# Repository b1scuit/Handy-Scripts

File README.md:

# B1scuit-Handy-Scripts
Just random things for random reasons

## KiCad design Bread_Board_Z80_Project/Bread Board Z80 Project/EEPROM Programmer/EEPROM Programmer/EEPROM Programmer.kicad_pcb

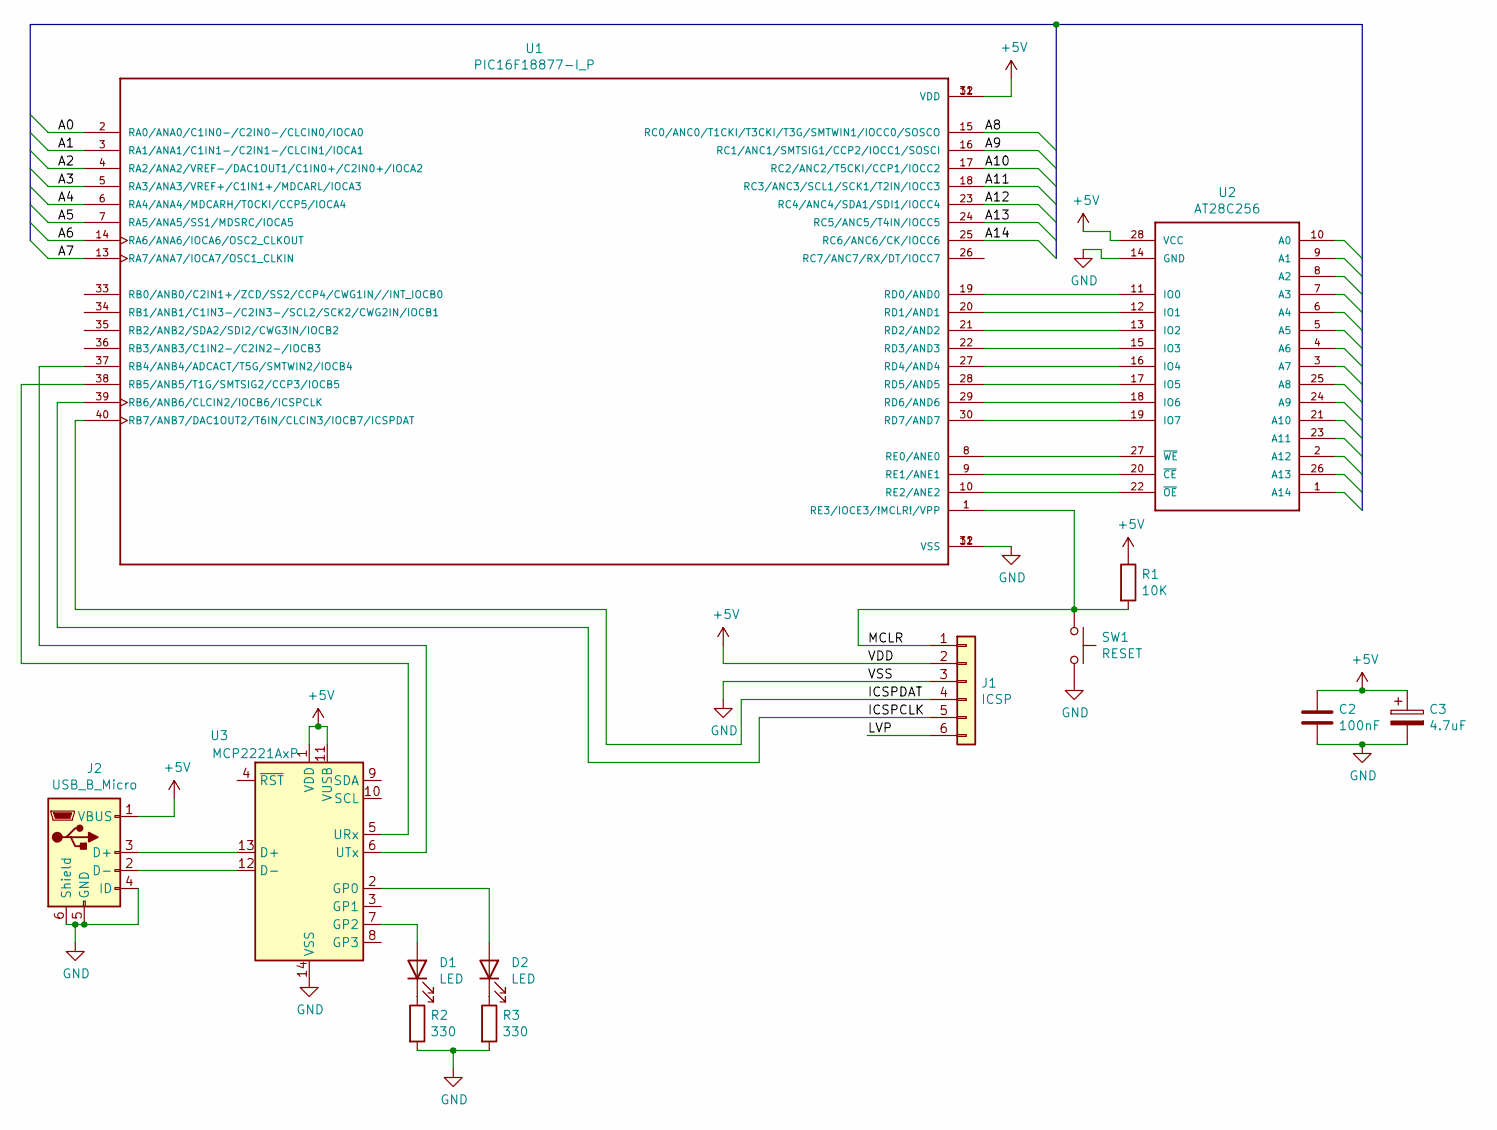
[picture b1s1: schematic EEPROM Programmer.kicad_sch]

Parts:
C2: 100nF; C_Rect_L7.0mm_W6.0mm_P5.00mm
C3: 4.7uF; C_Rect_L7.0mm_W6.0mm_P5.00mm
D1, D2: LED; LED_D8.0mm
J1: ICSP; PinHeader_1x06_P1.00mm_Horizontal
J2: USB_B_Micro; USB_Micro-AB_Molex_47590-0001
R1: 10K; R_Box_L8.4mm_W2.5mm_P5.08mm
R2, R3: 330; R_Box_L8.4mm_W2.5mm_P5.08mm
SW1: RESET; SW_SPDT_PCM12
U1: PIC16F18877-I_P; DIP-40_W15.24mm_LongPads
U2: AT28C256; DIP_Socket-28_W11.9_W12.7_W15.24_W17.78_W18.5_3M_228-1277-0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
U3: MCP2221AxP; DIP-14_W7.62mm

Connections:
+5V: C2.1, C3.1, J1.2, J2.1 (VBUS), R1.1, U1.11 (VDD), U1.32 (VDD), U2.28 (VCC), U3.1 (VDD), U3.11 (VUSB)
/A0: U1.2 (RA0/ANA0/C1IN0-/C2IN0-/CLCIN0/IOCA0)
/A1: U1.3 (RA1/ANA1/C1IN1-/C2IN1-/CLCIN1/IOCA1)
/A2: U1.4 (RA2/ANA2/VREF-/DAC1OUT1/C1IN0+/C2IN0+/I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)
/A3: U1.5 (RA3/ANA3/VREF+/C1IN1+/MDCARL/IOCA3)
/A4: U1.6 (RA4/ANA4/MDCARH/T0CKI/CCP5/IOCA4)
/A5: U1.7 (RA5/ANA5/SS1/MDSRC/IOCA5)
/A6: U1.14 (RA6/ANA6/IOCA6/OSC2_CLKOUT)
/A7: U1.13 (RA7/ANA7/IOCA7/OSC1_CLKIN)
/A8: U1.15 (RC0/ANC0/T1CKI/T3CKI/T3G/SMTWIN1/IOCC0/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)
/A9: U1.16 (RC1/ANC1/SMTSIG1/CCP2/IOCC1/SOSCI)
/A10: U1.17 (RC2/ANC2/T5CKI/CCP1/IOCC2)
/A11: U1.18 (RC3/ANC3/SCL1/SCK1/T2IN/IOCC3)
/A12: U1.23 (RC4/ANC4/SDA1/SDI1/IOCC4)
/A13: U1.24 (RC5/ANC5/T4IN/IOCC5)
/A14: U1.25 (RC6/ANC6/CK/IOCC6)
/ICSPCLK: J1.5, U1.39 (RB6/ANB6/CLCIN2/IOCB6/ICSPCLK)
/ICSPDAT: J1.4, U1.40 (RB7/ANB7/DAC1OUT2/T6IN/CLCIN3/IOCB7/ICS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)
/LVP: J1.6
/MCLR: J1.1, R1.2, SW1.1, U1.1 (RE3/IOCE3/!MCLR!/VPP)
GND: C2.2, C3.2, J1.3, J2.4 (ID), J2.5 (GND), J2.6 (Shield), R2.2, R3.2, SW1.2, U1.12 (VSS), U1.31 (VSS), U2.14 (GND), U3.14 (VSS)
unnamed: D1.2 (A), U3.7 (GP2)
unnamed: D1.1 (K), R2.1
unnamed: D2.2 (A), U3.2 (GP0)
unnamed: D2.1 (K), R3.1
unnamed: J2.3 (D+), U3.13 (D+)
unnamed: J2.2 (D-), U3.12 (D-)
unnamed: U1.37 (RB4/ANB4/ADCACT/T5G/SMTWIN2/IOCB4), U3.6 (UTx)
unnamed: U1.38 (RB5/ANB5/T1G/SMTSIG2/CCP3/IOCB5), U3.5 (URx)
unnamed: U1.19 (RD0/AND0), U2.11 (IO0)
unnamed: U1.20 (RD1/AND1), U2.12 (IO1)
unnamed: U1.21 (RD2/AND2), U2.13 (IO2)
unnamed: U1.22 (RD3/AND3), U2.15 (IO3)
unnamed: U1.27 (RD4/AND4), U2.16 (IO4)
unnamed: U1.28 (RD5/AND5), U2.17 (IO5)
unnamed: U1.29 (RD6/AND6), U2.18 (IO6)
unnamed: U1.30 (RD7/AND7), U2.19 (IO7)
unnamed: U1.8 (RE0/ANE0), U2.27 (~WE)
unnamed: U1.9 (RE1/ANE1), U2.20 (~CE)
unnamed: U1.10 (RE2/ANE2), U2.22 (~OE)

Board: 2 copper layers, 13 parts (0 on the bottom side), 24 nets, no tracks yet.

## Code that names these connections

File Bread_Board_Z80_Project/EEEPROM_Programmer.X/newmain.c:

/*
 * File:   newmain.c
 * Author: dysvi
 *
 * Created on 04 June 2020, 09:22
 */

// PIC16F18877 Configuration Bit Settings

// 'C' source line config statements

// CONFIG1
#pragma config FEXTOSC = HS     // External Oscillator mode selection bits (HS (crystal oscillator) above 4MHz; PFM set to high power)
#pragma config RSTOSC = HFINTPLL// Power-up default value for COSC bits (HFINTOSC with 2x PLL, with OSCFRQ = 16 MHz and CDIV = 1:1 (FOSC = 32 MHz))
#pragma config CLKOUTEN = OFF   // Clock Out Enable bit (CLKOUT function is disabled; i/o or oscillator function on OSC2)
#pragma config CSWEN = ON       // Clock Switch Enable bit (Writing to NOSC and NDIV is allowed)
#pragma config FCMEN = ON       // Fail-Safe Clock Monitor Enable bit (FSCM timer enabled)

// CONFIG2
#pragma config MCLRE = ON       // Master Clear Enable bit (MCLR pin is Master Clear function)
#pragma config PWRTE = OFF      // Power-up Timer Enable bit (PWRT disabled)
#pragma config LPBOREN = OFF    // Low-Power BOR enable bit (ULPBOR disabled)
#pragma config BOREN = ON       // Brown-out reset enable bits (Brown-out Reset Enabled, SBOREN bit is ignored)
#pragma config BORV = LO        // Brown-out Reset Voltage Selection (Brown-out Reset Voltage (VBOR) set to 1.9V on LF, and 2.45V on F Devices)
#pragma config ZCD = OFF        // Zero-cross detect disable (Zero-cross detect circuit is disabled at POR.)
#pragma config PPS1WAY = ON     // Peripheral Pin Select one-way control (The PPSLOCK bit can be cleared and set only once in software)
#pragma config STVREN = ON      // Stack Overflow/Underflow Reset Enable bit (Stack Overflow or Underflow will cause a reset)

// CONFIG3
#pragma config WDTCPS = WDTCPS_31// WDT Period Select bits (Divider ratio 1:65536; software control of WDTPS)
#pragma config WDTE = ON        // WDT operating mode (WDT enabled regardless of sleep; SWDTEN ignored)
#pragma config WDTCWS = WDTCWS_7// WDT Window Select bits (window always open (100%); software control; keyed access not required)
#pragma config WDTCCS = SC      // WDT input clock selector (Software Control)

// CONFIG4
#pragma config WRT = OFF        // UserNVM self-write protection bits (Write protection off)
#pragma config SCANE = available// Scanner Enable bit (Scanner module is available for use)
#pragma config LVP = ON         // Low Voltage Programming Enable bit (Low Voltage programming enabled. MCLR/Vpp pin function is MCLR.)

// CONFIG5
#pragma config CP = OFF         // UserNVM Program memory code protection bit (Program Memory code protection disabled)
#pragma config CPD = OFF        // DataNVM code protection bit (Data EEPROM code protection disabled)

#define _XTAL_FREQ 32000000
// #pragma config statements should precede project file includes.
// Use project enums instead of #define for ON and OFF.

#define ADDRLOW PORTA
#define ADDRHIGH PORTC
#define DATA PORTD
#define WE RE0
#define OE RE1
#define CE RE2


#include <xc.h>
#include <stdint.h>



void setaddress(uint8_t *in) {
    ADDRLOW = *in;
}
void setup(){
    // Sets up the 3 7 bit buses and the 3 bit bus
    ANSELA = ANSELC = ANSELD = ANSELE = 0x00;
    TRISA = TRISC = TRISD = TRISE = 0x00;
}


void main(void) { 
    setup(); // Set up all the outputs
    
    uint8_t counter = 0x00 ;
    // Run the main function and as soon as its finished, run it again
    while(1) {
        setaddress(&counter);
        counter = counter + 1 ;
        
        __delay_ms(1000);
    }
    return;
}

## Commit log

2016-11-12 Added THP2 setup document Changes to be committed: new file: PenTesting/THP2/setup.txt
2016-11-12 Added dotfiles and system scripts
    Changes to be committed:
    new file: dotFiles/i3-gaps-main-system/.Xauthority
    new file: dotFiles/i3-gaps-main-system/.Xdefaults
    new file: dotFiles/i3-gaps-main-system/.Xdefaults.save
    new file: dotFiles/i3-gaps-main-system/.Xresources
    new file: dotFiles/i3-gaps-main-system/.config/i3/config
2016-11-12 Woops Changes to be committed: deleted: .Xauthority deleted: .Xdefaults.save deleted: .zcompdump deleted: .zcompdump-B1scuit-PC-5.1.1 deleted: .zsh-update deleted: .zsh_history
2016-11-12 Added some scripts Changes to be committed: new file: bashScripts/colourScript.sh new file: bashScripts/dirSize.sh
2016-11-13 Updated colours on output Changes to be committed: modified: colourScript.sh
2016-11-14 I have no idea Changes to be committed: new file: I2C/.i2cTalk.cpp.swp new file: I2C/i2c.cpp new file: bashScripts/responderParams.sh
2016-11-23 Changes to be committed: new file: Security-Practicals/get.php new file: Security-Practicals/getAction.php new file: Security-Practicals/post.php new file: Security-Practicals/post1Action.php new fil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
2016-11-23 Potential exploit on get.php
    Changes to be committed:
    new file: Security-Practicals/information/get.php.text
2016-12-29 new file: misc/PHP-obj-arr.php
2016-12-29 modified: misc/PHP-obj-arr.php
2016-12-29 new file: misc/PHP-obj-arr-2.php
2016-12-29 modified: misc/PHP-obj-arr-2.php
2016-12-30 modified: misc/PHP-obj-arr-2.php modified: misc/PHP-obj-arr.php
2016-12-30 modified: misc/PHP-obj-arr-2.php new file: misc/lib/User.php new file: misc/lib/controllerClass.php
2016-12-30 modified: misc/PHP-obj-arr-2.php modified: misc/lib/User.php
2016-12-30 modified: misc/lib/controllerClass.php
2016-12-30 modified: misc/PHP-obj-arr-2.php new file: misc/PHP-obj-arr-2.sql
2016-12-30 modified: misc/PHP-obj-arr-2.php modified: misc/PHP-obj-arr-2.sql modified: misc/lib/User.php
2016-12-30 renamed: misc/PHP-obj-arr-2.php -> misc/obj-array/PHP-obj-arr-2.php renamed: misc/PHP-obj-arr-2.sql -> misc/obj-array/PHP-obj-arr-2.sql renamed: misc/lib/User.php -> misc/obj-array/lib/User.php renam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
2016-12-30 renamed: misc/PHP-obj-arr.php -> misc/obj-array/PHP-obj-arr.php
2016-12-30 new file: misc/never-use-this/_htaccess new file: misc/never-use-this/application/controllers/Library.php new file: misc/never-use-this/application/controllers/index.php new file: misc/never-use-this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
2017-01-02 new file: bashScripts/trollScripts.txt
2017-01-02 modified: bashScripts/trollScripts.txt
2017-01-09 new file: PenTesting/IDS-Circumvent.sh
2017-01-09 modified: PenTesting/IDS-Circumvent.sh
2017-01-10 modified: PenTesting/IDS-Circumvent.sh new file: PenTesting/README.md
2017-01-12 new file: PenTesting/server-py-instructions
2017-01-12 modified: PenTesting/server-py-instructions
2017-01-12 Changes to be committed: new file: .miniIDS.sh.swp new file: IDS-Circumvent-output.txt modified: IDS-Circumvent.sh new file: active.txt new file: available.txt new file: miniIDS.sh
2017-01-13 Changes to be committed: new file: changeBrightness.sh
    Changes not staged for commit:
    deleted: ../PenTesting/.miniIDS.sh.swp
    modified: ../PenTesting/active.txt
    modified: ../PenTesting/available.txt
2017-01-19 Changes to be committed: deleted: PenTesting/IDS-Circumvent-output.txt deleted: PenTesting/active.txt deleted: PenTesting/available.txt deleted: PenTesting/miniIDS.sh new file: bashScripts/tputtest.s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
2017-01-24 modified: bashScripts/changeBrightness.sh new file: bashScripts/extIp.sh new file: bashScripts/mouseSensitivityNerf.sh
2017-01-24 deleted: echo deleted: zenity
2017-01-26 Added this for indexing in apache
2017-01-26 modified: misc/obj-array/PHP-obj-arr-2.php modified: misc/obj-array/lib/controllerClass.php new file: misc/obj-array/lib/loader.php renamed: misc/obj-array/lib/User.php -> misc/obj-array/lib/users.php
2017-01-26 Changes to be committed: new file: dotFiles/i3-gaps-laptop/.Xdefaults new file: dotFiles/i3-gaps-laptop/.Xresources new file: dotFiles/i3-gaps-laptop/.config/i3/config new file: dotFiles/i3-gaps-lapt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
2017-01-26 Changes to be committed: new file: dotFiles/i3-gaps-laptop/.oh-my-zsh/.zshrc
2017-01-26 Changes to be committed: modified: package-list.txt
2017-02-04 new file: i3-gaps
2017-05-05 new file: .gitignore new file: I2C/LCD/index.js new file: I2C/LCD/package.json deleted: I2C/i2c.cpp
2017-05-05 modified: I2C/LCD/index.js modified: I2C/LCD/package.json
2017-05-05 modified: I2C/LCD/index.js
2017-05-07 modified: .gitignore modified: I2C/LCD/index.js modified: I2C/LCD/package.json
2017-06-12 modified: I2C/LCD/package.json new file: I2C/Project/.gitignore new file: I2C/Project/include/FRAM_lib.h new file: I2C/Project/include/LIS3DH_lib.h new file: I2C/Project/makefile new file: I2C/Projec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
2017-06-12 Alignment issue
2017-10-03 Added .vimrc
2017-10-08 ssss
2017-10-09 whatever the fuck
2017-10-11 added search
2017-10-31 Vimrc update
2018-01-04 Added pormpt command
2018-01-04 Changed how prompt part works
2018-01-05 Added PHP script
2018-01-06 Added Maltego robot.txt finder
2018-01-10 Reordered things a bit
2018-01-10 Added MySQL DIr Python package
2018-01-10 Added start of I2C library for future use
2018-01-10 Added int constructor
2018-02-26 Updated vimrc
2018-03-08 Added OSX vimc
2018-04-03 Added vimrc files
2018-04-09 Added small inside vim check
2018-04-09 Vimrc adjustments + eventually making corss compatible
2018-04-09 Added airline themes
2018-04-12 Organised vim
2018-04-12 Moved specific vim settings to seperate file
2018-04-12 OPtimised themes
2018-04-12 Adjusted comment
2018-04-12 Changed how PHP syntax higlighting in HTML files works
2018-04-12 Spacing
2018-04-16 Minor adjustments
2018-04-16 pointless as shift+* does same thing, removing since functionality already built in
2018-04-16 Added fugative for GIT branch in Airline
2018-04-18 Removed prexisting functionality and unused functions
2018-04-19 Removed nocompatible [as advised](https://www.reddit.com/r/vim/comments/8d9bh1/vimrc_review_thread_40/dxmj1z1/)
2018-04-19 Removed nocompatible as advised
    https://www.reddit.com/r/vim/comments/8d9bh1/vimrc_review_thread_40/dxmj1z1/
2018-04-20 Implemented feedback
    https://www.reddit.com/r/vim/comments/8d9bh1/vimrc_review_thread_40/dxmtei6/
2018-04-20 Implemented solution implemented E216: No such event: fugitiveblame call s:BlameSyntax() fix
2018-04-20 Implemented feedback https://www.reddit.com/r/vim/comments/8d9bh1/vimrc_review_thread_40/dxoipz9/
2018-04-23 Added dotfiles
2018-07-05 Update .vimrc
    Added dragable splits
2018-07-05 Update .vimrc
    Added in netrw commands so when using :Lexplore it mimics NERDTree functionality
2018-07-06 Added startpage
2018-07-18 Added theme
2018-07-18 Added emoji for git repo status because why not xD
2018-11-10 Added stuff
2020-01-17 things
2020-01-20 qwertyuiop
2020-01-23 Added osci script
2020-01-23 Changed perms
2020-02-24 Added thung
2023-06-18 Added Z80 breadboard project
2023-06-18 Added
2023-06-18 Added Z80 sc
2023-07-11 Thing
2023-07-11 added devops
2023-07-13 Tweaks
2023-07-13 Add reloop
2023-07-13 Checked numbering
2023-07-13 Change counter
2023-07-13 try again
